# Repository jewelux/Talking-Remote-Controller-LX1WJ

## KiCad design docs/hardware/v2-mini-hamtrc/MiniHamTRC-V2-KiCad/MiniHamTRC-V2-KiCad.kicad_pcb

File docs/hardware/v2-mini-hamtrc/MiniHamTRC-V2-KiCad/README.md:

# MiniHamTRC-V2-KiCad – KiCad project of the Mini-HamTRC V2

The KiCad source files of the Mini-HamTRC V2: schematic, PCB and the project's own symbol and footprint
libraries. Made with **KiCad 10.0**.

| File | Content |
|---|---|
| `MiniHamTRC-V2-KiCad.kicad_pro` | project – open this one in KiCad |
| `MiniHamTRC-V2-KiCad.kicad_sch` | schematic, the source of [`../circuit-diagram-V2.pdf`](../circuit-diagram-V2.pdf) |
| `MiniHamTRC-V2-KiCad.kicad_pcb` | PCB, see *Status* below |
| `sym-lib-table`, `fp-lib-table` | point KiCad to the libraries in `libraries/` |
| `libraries/_MyLibraryLX1WJ.kicad_sym` | symbols used by the schematic |
| `libraries/footprints/` | footprints used by the PCB (suffix `_CNC`: pads sized for a milled board) |

The folder is self-contained: the library tables use `${KIPRJMOD}/libraries/...`, so the project opens on any
computer without installing extra libraries. From KiCad's standard libraries come only the connector symbols of
J4, J5 and J8 (also stored in the schematic), the TO-92 footprint of Q1 and the 3D models.

## Status

- **Schematic:** current V2, as in [`../circuit-diagram-V2.pdf`](../circuit-diagram-V2.pdf), including R5, 12 kΩ,
  between the MAX3232's RXD and GPIO 9. [`../hardware_wiring_v2.md`](../hardware_wiring_v2.md) describes every
  connection in words, and [`../bom_v2.md`](../bom_v2.md) lists the parts.
- **Power:** J5 "VCC In 5V" is the external 5 V input, pin 1 +5 V, pin 2 GND. Which socket or cable goes to J5 on
  the box is up to the builder. C6, 470 µF electrolytic, and C5, 100 nF ceramic, are in parallel on the 5 V rail.
  C6 uses the plain capacitor symbol and the 5 mm disc footprint, which has no polarity mark: minus goes to pad 2, GND.
- **PCB:** a two-layer layout routed with Freerouting. It has not been made or tested yet. The boards built so far
  are the single-sided layout in [`../pcb-layout-V2.pdf`](../pcb-layout-V2.pdf).
- **ERC:** three "power pin not driven" errors at U1 (3V3, 5V0, GND), because the schematic has no `PWR_FLAG`
  symbols. The supply comes from J5 and the ESP32 board, so they are harmless.
- **DRC:** no unconnected items, schematic and PCB in parity; warnings only (mostly silkscreen over copper).

The GPIO mapping is the same as in [`firmware/config_pins.h`](../../../../firmware/config_pins.h).
Questions are welcome: [open a build enquiry](https://github.com/jewelux/Talking-Remote-Controller-LX1WJ/issues/new?template=build-enquiry.yml).

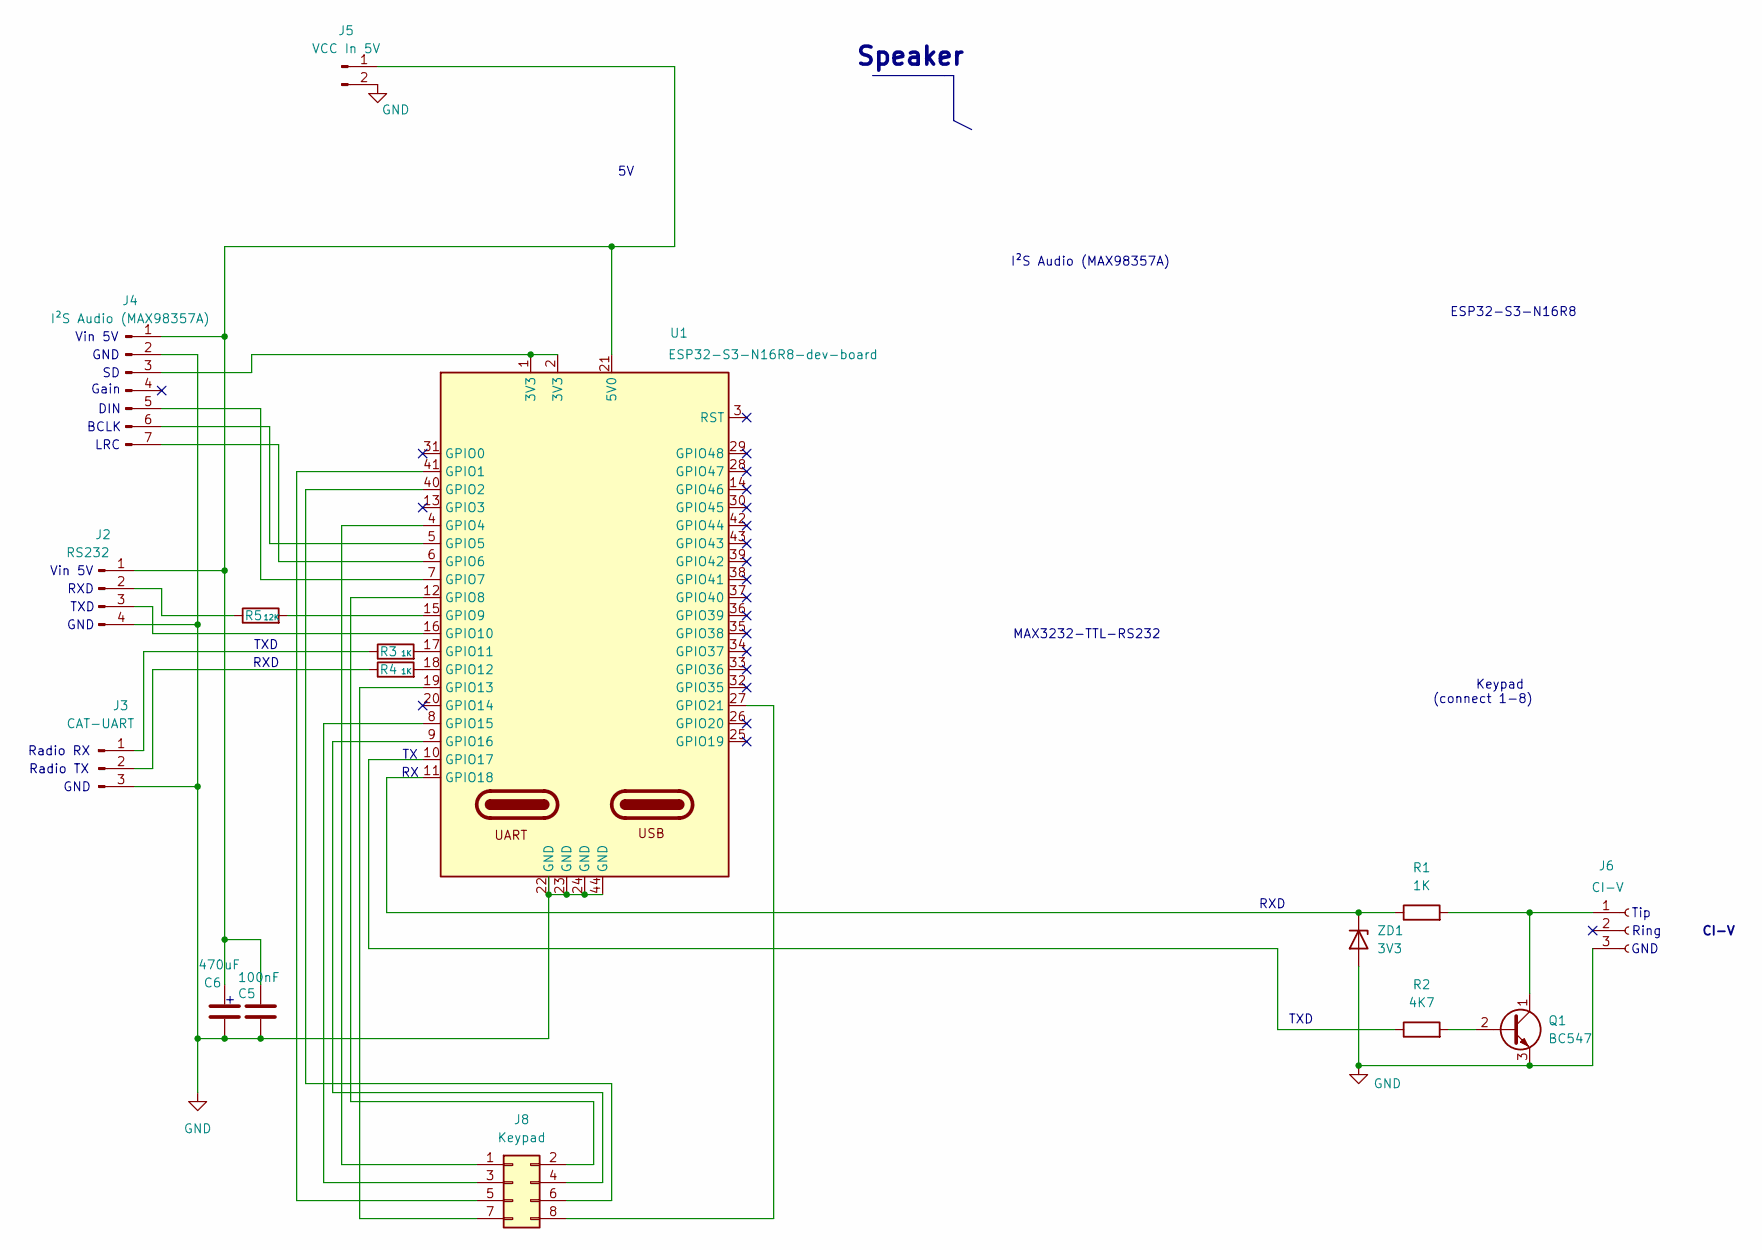
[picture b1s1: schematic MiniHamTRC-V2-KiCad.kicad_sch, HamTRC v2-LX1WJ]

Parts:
C5: 100nF; C_Disc_D4.7mm_W2.5mm_P5.00mm_CNC
C6: 470uF; C_Disc_D4.7mm_W2.5mm_P5.00mm_CNC
J2: RS232; PinHeader_RS232Module_CNC
J3: CAT-UART; Jack_3.5mm_CUI_SJ1-3525N_Horizontal_CNC
J4: I²S Audio (MAX98357A); PinHeader_1x07_P2.54mm_Vertical_CNC
J5: VCC In 5V; PinHeader_1x02_P2.54mm_Vertical_CNC
J6: CI-V; Jack_3.5mm_CUI_SJ1-3525N_Horizontal_CNC
J8: Keypad; PinHeader_2x04_P2.54mm_Vertical_CNC
Q1: BC547; TO-92_Inline
R1, R3, R4: 1K; R_Axial_DIN0207_L6.3mm_D2.5mm_P10.16mm_Horizontal_CNC
R2: 4K7; R_Axial_DIN0207_L6.3mm_D2.5mm_P10.16mm_Horizontal_CNC
R5: 12K; R_Axial_DIN0207_L6.3mm_D2.5mm_P10.16mm_Horizontal_CNC
U1: ESP32-S3-N16R8-dev-board; ESP32-S3-DevKitC_N16R8_CNC
ZD1: 3V3; ZD_DO-35_SOD27_P7.62mm_Horizontal_CNC

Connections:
GND: C5.2, C6.2, J2.4, J3.3, J4.2, J5.2, J6.3, Q1.3 (E), U1.22 (GND), U1.23 (GND), U1.24 (GND), U1.44 (GND), ZD1.2 (A)
unnamed: C5.1, C6.1, J2.1, J4.1, J5.1, U1.21 (5V0)
unnamed: J2.2, R5.1
unnamed: J2.3, U1.16 (GPIO10)
unnamed: J3.1, R3.1
unnamed: J3.2, R4.1
unnamed: J4.3, U1.1 (3V3), U1.2 (3V3)
unnamed: J4.5, U1.7 (GPIO7)
unnamed: J4.6, U1.5 (GPIO5)
unnamed: J4.7, U1.6 (GPIO6)
unnamed: J6.1, Q1.1 (C), R1.2
unnamed: J8.1, U1.4 (GPIO4)
unnamed: J8.2, U1.12 (GPIO8)
unnamed: J8.3, U1.8 (GPIO15)
unnamed: J8.4, U1.9 (GPIO16)
unnamed: J8.5, U1.41 (GPIO1)
unnamed: J8.6, U1.40 (GPIO2)
unnamed: J8.7, U1.19 (GPIO13)
unnamed: J8.8, U1.27 (GPIO21)
unnamed: Q1.2 (B), R2.2
unnamed: R5.2, U1.15 (GPIO9)
unnamed: R3.2, U1.17 (GPIO11)
unnamed: R4.2, U1.18 (GPIO12)
unnamed: R2.1, U1.10 (GPIO17)
unnamed: R1.1, U1.11 (GPIO18), ZD1.1 (K)

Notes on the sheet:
TXD
RXD
CI-V
Ring
Radio TX
Vin 5V
MAX3232-TTL-RS232
Radio RX
LRC
GND
DIN
ESP32-S3-N16R8
BCLK
Speaker
Tip
Keypad (connect 1-8)
Gain
I²S Audio (MAX98357A)

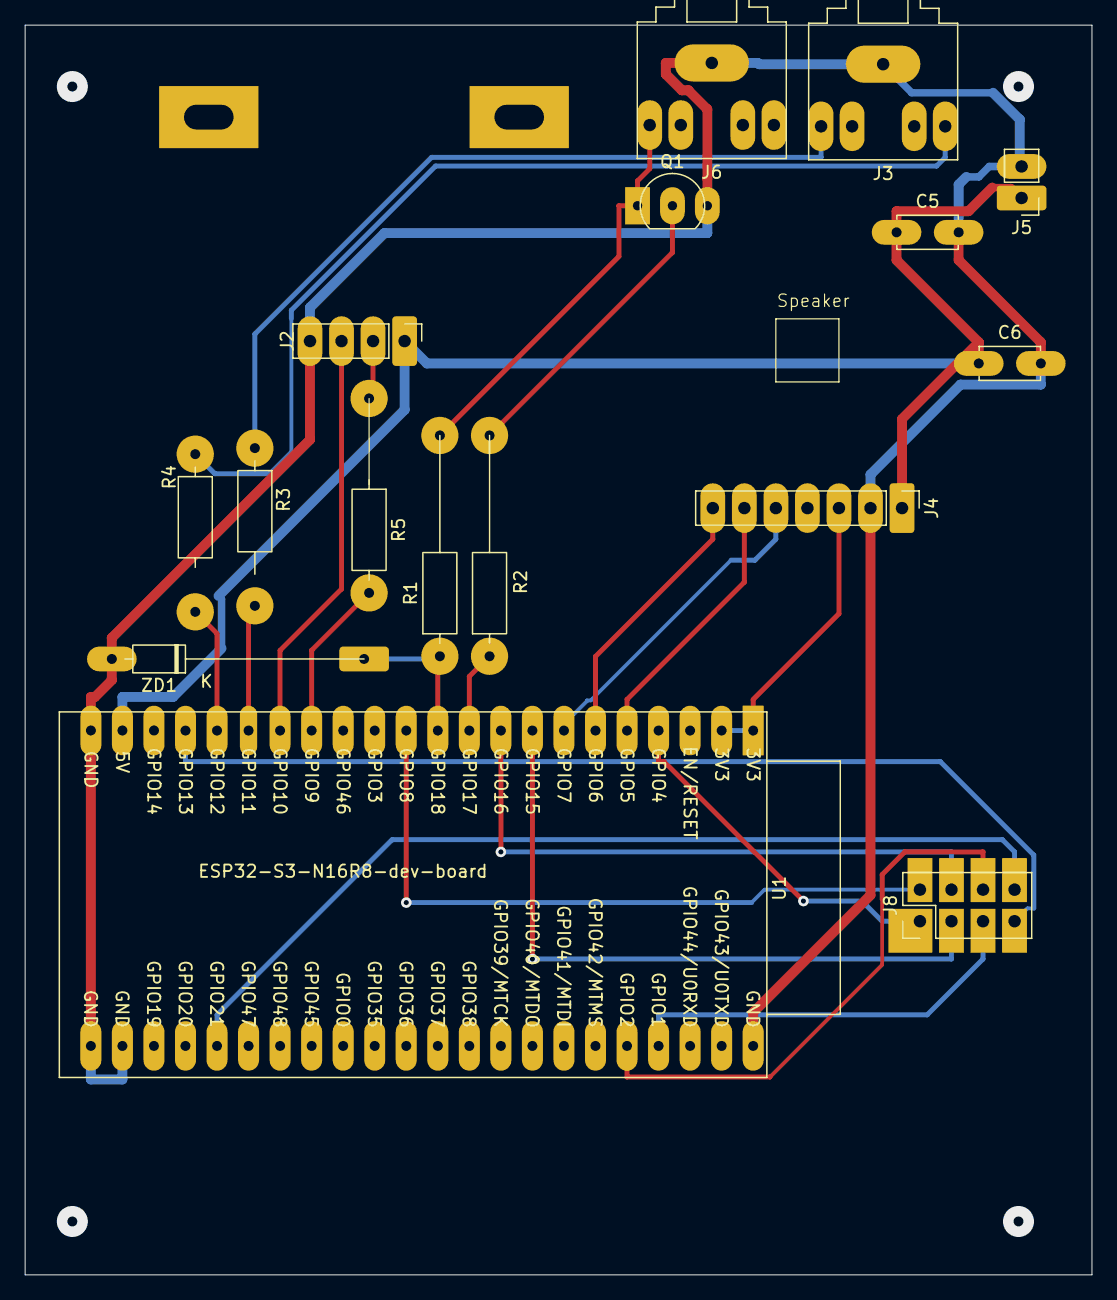
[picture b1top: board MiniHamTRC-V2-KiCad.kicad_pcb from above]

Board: 2 copper layers, 85.9 x 100.6 mm, 16 parts (0 on the bottom side), 25 nets.

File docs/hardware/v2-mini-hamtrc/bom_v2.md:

# Bill of Materials – HamTRC V2 (Mini-HamTRC)

> [!IMPORTANT]
> **This page describes the current Mini-HamTRC V2 (`development` branch).**
> The `main` branch still contains the first prototype (V1, with SD card). Do not use `main` for a V2 build.
> A step-by-step build page written for screen readers is at [lx1wj.eu – Build a Mini-HamTRC](https://lx1wj.eu/hamtrc/mini-review/index-en.html)
> (also in [German](https://lx1wj.eu/hamtrc/mini-review/index.html) and [French](https://lx1wj.eu/hamtrc/mini-review/index-fr.html)).
> Questions are welcome: [open a build enquiry](https://github.com/jewelux/Talking-Remote-Controller-LX1WJ/i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

> **Status: current V2 build (2026-11-25).** Derived from [`circuit-diagram-V2.pdf`](circuit-diagram-V2.pdf)
> and [`pcb-layout-V2.pdf`](pcb-layout-V2.pdf), plus the parts added since (marked \*). Wiring details: [`hardware_wiring_v2.md`](hardware_wiring_v2.md).
> KiCad source files: [`MiniHamTRC-V2-KiCad/`](MiniHamTRC-V2-KiCad/).

## Modules

| Ref | Qty | Part | Notes |
|---|---|---|---|
| U1 | 1 | ESP32-S3-N16R8 dev board (DevKitC-1 style, 2×22 pins, dual USB-C) | 16 MB flash / 8 MB PSRAM required by firmware |
| J4 | 1 | MAX98357A I2S class-D amplifier breakout (7 pins) | e.g. Adafruit #3006 or clone |
| J2 | 1 | MAX3232 TTL ↔ RS-232 module with DB9 (4 pins: GND, RXD, TXD, VCC) | |
| J8 | 1 | 4×4 membrane matrix keypad, 8-pin connector | |
| – | 1 | Speaker 4–8 Ω, ≥ 1 W | to the MAX98357A screw terminal |

## Discrete components

| Ref | Qty | Value | Part / Package | Function |
|---|---|---|---|---|
| R1 | 1 | 1 kΩ | resistor ¼ W, axial THT | CI-V receive series resistor |
| R2 | 1 | 4.7 kΩ | resistor ¼ W, axial THT | CI-V transmit base resistor |
| R3 | 1 | 1 kΩ | resistor ¼ W, axial THT | CAT-TTL TX series resistor |
| R4 | 1 | 1 kΩ | resistor ¼ W, axial THT | CAT-TTL RX series resistor |
| ZD1 | 1 | 3.3 V | Zener diode, e.g. BZX55C3V3 / BZX79C3V3, DO-35 | CI-V RX clamp |
| D1 | – | – | wire link (PCB footprint only, no diode) | 5 V from J5 to the rail |
| Q1 | 1 | BC547 | NPN, TO-92 (BC548 / BC549 also fine) | CI-V open-collector driver |
| C5 | 1 | 100 nF | ceramic capacitor, THT | 5 V rail decoupling |
| \* | 1 | 220 µF | electrolytic capacitor, ≥ 10 V | MAX98357A `Vin` decoupling, close to the module |
| \* | 1 | 100 nF | ceramic capacitor, THT | MAX98357A `Vin` decoupling, close to the module |
| R5 | 1 | 12 kΩ | resistor ¼ W, axial THT (variant B, as in the schematic) | GPIO 9 protection: RXD → GPIO 9 |
| \* | (1 + 1) | 4.7 kΩ + 10 kΩ | resistors ¼ W (variant A, instead of R5) | GPIO 9 protection: 4.7 kΩ RXD → GPIO 9, 10 kΩ GPIO 9 → GND |

## Connectors

| Ref | Qty | Part | Function |
|---|---|---|---|
| J5 | 1 | 2-pin header or terminal, 2.54 mm | 5 V power input |
| J6 | 1 | 3.5 mm stereo jack, PCB mount | CI-V (Tip = bus, Sleeve = GND) |
| J3 | 1 | 3.5 mm stereo jack, PCB mount | CAT-TTL |
| J8 | 1 | 2×4 pin header, 2.54 mm | keypad |
| – | 2 | female header 1×22, 2.54 mm | socket for U1 |
| – | 1 | female header 1×7, 2.54 mm | socket for J4 (MAX98357A) |
| – | 1 | female header 1×4, 2.54 mm | socket for J2 (MAX3232) |

## PCB and mechanics

| Qty | Item | Notes |
|---|---|---|
| 1 | PCB HamTRC V2, single-sided | per `pcb-layout-V2.pdf` |
| 6 | wire bridges (tinned copper wire) | red links in the layout PDF (+1 for D1 if no diode) |
| 4 | M3 spacers + screws | corner mounting holes |
| 1 | 5 V supply, at least 1 A | good, stable plug-in supply; socket or cable to J5 as the builder prefers |
| 1 | USB data cable for the ESP32 board | only for flashing the firmware from a computer |
| – | cables: 3.5 mm stereo cable (CI-V / CAT), DB9 cable (RS-232) | depending on radio |

## Notes

- The Mini is powered from an external 5 V supply on J5. The USB-C ports of the
  ESP32-S3 board are only used to flash the firmware; powered through them, the MAX modules do not get a proper
  supply (issues #29, #31). See `hardware_wiring_v2.md`, section 1.
- D1 is not in the schematic any more; the PCB keeps its footprint. Fit a wire link.
- Do not close the USB-OTG solder bridge on the ESP32-S3 board; USB control of radios comes with V3.
- RS-232 cable: Yaesu FTDX10 needs a null modem cable or adapter, Yaesu FT-847 a straight cable.
- The MAX3232 module is soldered onto the two large pads at the top edge of the PCB.
- The SD-card module of V1 is no longer part of V2.
